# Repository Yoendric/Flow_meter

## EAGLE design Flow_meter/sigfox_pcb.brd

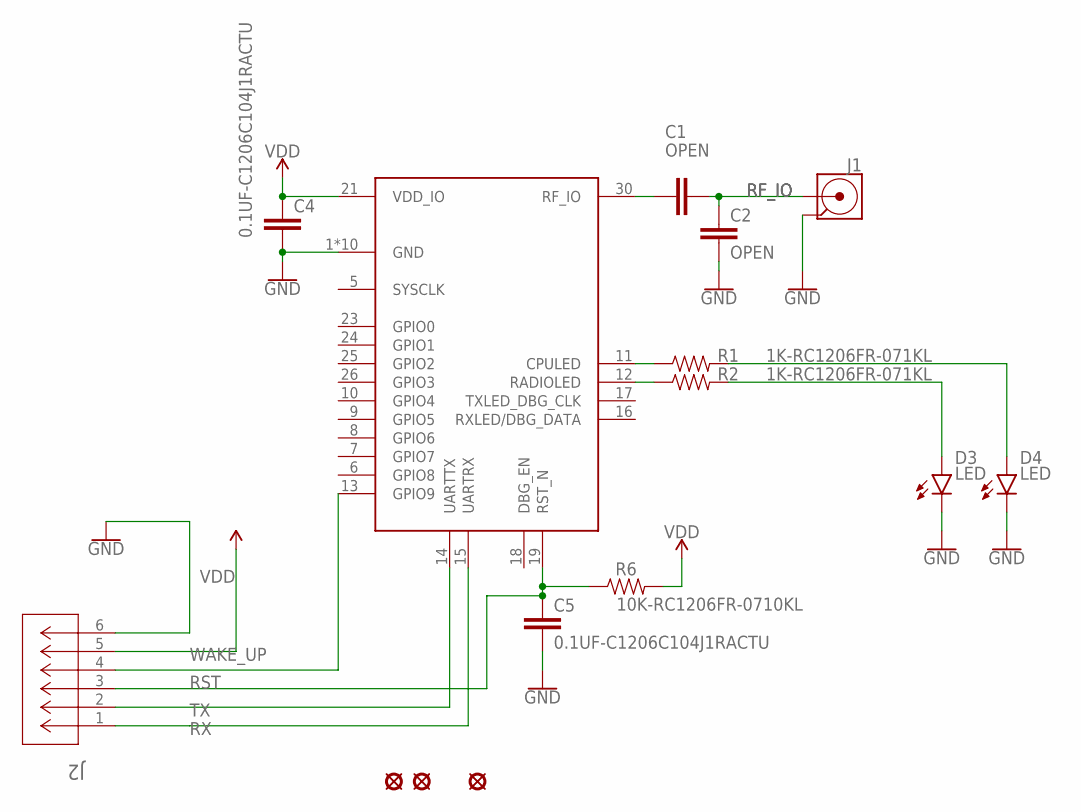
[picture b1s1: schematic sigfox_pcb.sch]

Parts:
C1, C2: OPEN; C1206_OPEN
C4, C5: 0.1UF-C1206C104J1RACTU; C1206
D3, D4: LED; LED1206
H1, H2, H4: HOLE-M3; HOLE_3.0
J1: SMA-142-0701-801; 142-0701-801
J2: SSW-106-02-G-S-RA; CON6_1X6_TR_SSQ
R1, R2: 1K-RC1206FR-071KL; R1206
R6: 10K-RC1206FR-0710KL; R1206
U1: SFM11R2D

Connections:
GND: C2.2, C4.2, C5.2, D3.K (C), D4.K (C), J1.2_1 (2), J1.2_2 (2), J1.3_1 (2), J1.3_2 (2), J2.6, U1.1 (GND), U1.2 (GND), U1.3 (GND), U1.4 (GND), U1.20 (GND), U1.22 (GND), U1.27 (GND), U1.28 (GND), U1.29 (GND), U1.31 (GND)
unnamed: R1.1, U1.11 (CPULED)
unnamed: R2.1, U1.12 (RADIOLED)
unnamed: D3.A, R2.2
unnamed: D4.A, R1.2
unnamed: C1.1, U1.30 (RF_IO)
RF_IO: C1.2, C2.1, J1.1
RST: C5.1, J2.3, R6.1, U1.19 (RST_N)
RX: J2.1, U1.15 (UARTRX)
TX: J2.2, U1.14 (UARTTX)
VDD: C4.1, J2.5, R6.2, U1.21 (VDD_IO)
WAKE_UP: J2.4, U1.13 (GPIO9)

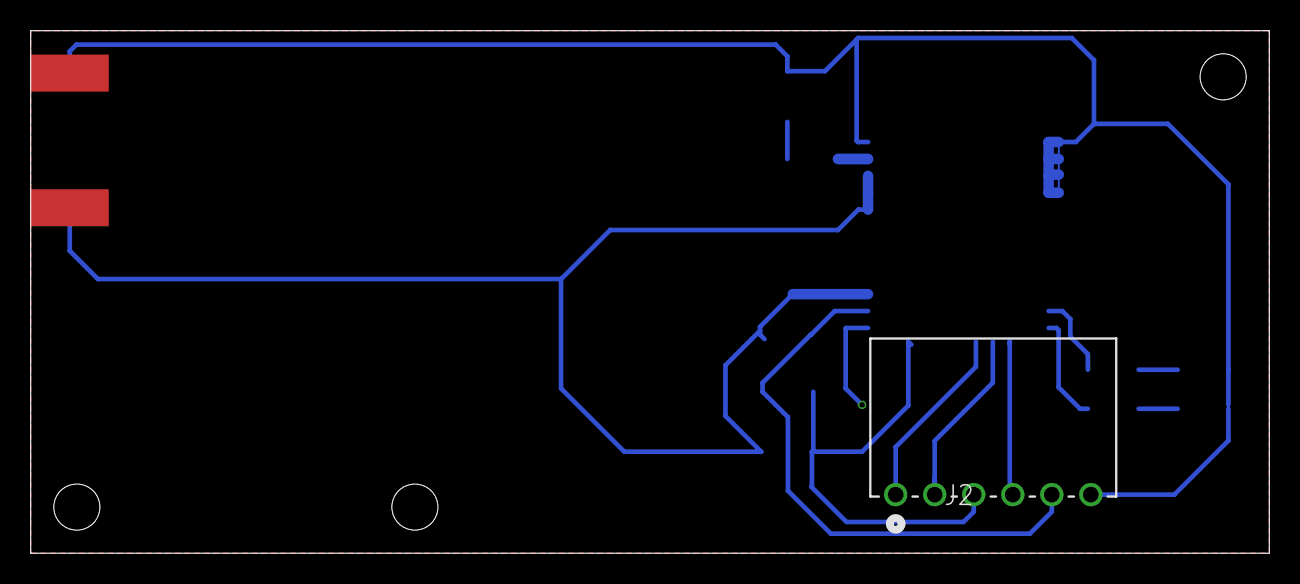
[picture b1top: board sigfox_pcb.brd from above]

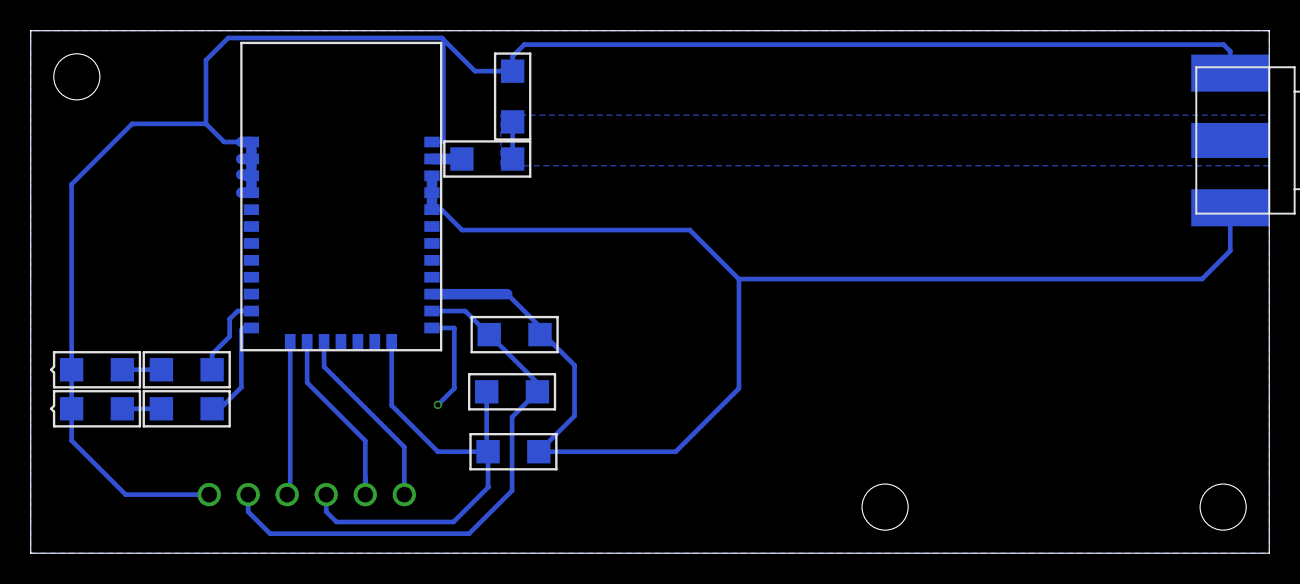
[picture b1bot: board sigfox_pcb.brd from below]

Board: 2 copper layers, 80.6 x 34.0 mm, 15 parts (11 on the bottom side), 12 nets.

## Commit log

2020-04-03 Actualizacion RTC wake up
2020-04-07 RTC Alarm ready
2020-04-10 First firmware micro Real
2020-04-16 I2c add
2020-09-20 Software con downlink sigfox (Polling/Interrup)
